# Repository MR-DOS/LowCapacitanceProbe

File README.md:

# LowCapacitanceProbe

## THIS DESIGN IS STILL UNDER CONSTRUCTION, ANY EXPORTED DATA ARE NON-FINAL AND ARE LIKELY NOT TO WORK. DO NOT ATTEMPT TO BUILD THIS DEVICE UNTIL THIS NOTICE DISAPPEARS! ALL IMAGES ARE PLACEHOLDERS AND MAY NOT FULLY REPRESENT THE REAL DEVICE AND MAY BE OUT OF SYNC WITH THE DESIGN DATA!

## USABLE DATA WILL BE PRESENT IN RELEASES TAB.

## 1+ GHz AC Probe with low input capacitance (less than 1 pF, hopefully)

2 dB flatness should be approx. 1.6 GHz, 3 dB flatness should be about 2.1 GHz, 6 dB flatness should be about 3.3 GHz. Design needs to be verified in reality (simulation is likely over-optimistic). In-band flatness should be better than 0.2 dB. Lower 6 dB corner should be at about 30 kHz while 3 dB corner is at about 50 kHz. The design should have fairly low noise, at least above 1 MHz.

Drawn in KiCAD 9.0.x, simulated in LTspice 17.x / 24.x.

## Expected issues

* Large noise at < 1 MHz due to thermal noise of 1M bias resistor
* Incorrect impedance of 50R traces
* Incorrect output impedance
* Possible instability of BF998 / spectrum peaking
* Bad linearity, especially due to use of varactor and resistor instead of current sink in source of BF998
* Large variance of parameters due to use of BF998

## Known issues which will be present

* No box yet (has to be covered in conductive material)
* Usage of obsolete part which is difficult to obtain (BF998)
* Component values not tried, will be suboptimal
* Varactor will probably need to be changed
* Needed manual calibration using a VNA and some tools
* Potentiometers not delinearised yet

## Board images (rendered)

## Live on-line project browser

[KiCanvas project viewer, disable layer Dwgs.User, view is not 1:1 with KiCAD](https://kicanvas.org/?github=https%3A%2F%2Fgithub.com%2FMR-DOS%2FLowCapacitanceProbe%2Ftree%2Fmain)

## Schematic

[Schematic SVG](https://github.com/MR-DOS/LowCapacitanceProbe/raw/main/Exports/Schematic/LowCapacitanceProbe.svg)

[Schematic PDF](https://github.com/MR-DOS/LowCapacitanceProbe/raw/main/Exports/Schematic/LowCapacitanceProbe.pdf)

## PCB drawing image

## 3D models

[STEP with solder mask, pads and copper fills (save to view)](https://github.com/MR-DOS/LowCapacitanceProbe/raw/main/Exports/3D/board.step)

[Simplified STEP (save to view)](https://github.com/MR-DOS/LowCapacitanceProbe/raw/main/Exports/3D/simplified/simplified.step)

## Board Shape

[DXF with board shape (save to view)](https://github.com/MR-DOS/LowCapacitanceProbe/raw/main/Exports/DXF/LowCapacitanceProbe-Edge_Cuts.dxf)

## Gerbers for production

[Zipped Gerbers](https://github.com/MR-DOS/LowCapacitanceProbe/raw/main/Exports/Gerbers/ZIP/LowCapacitanceProbe_v1.0.0.zip)

[Non-zipped Gerbers](https://github.com/MR-DOS/LowCapacitanceProbe/raw/main/Exports/Gerbers/)

## BOM

[Interactive BOM (save to view)](https://github.com/MR-DOS/LowCapacitanceProbe/raw/main/Exports/BOM/LowCapacitanceProbe_Interactive_BOM.html)

[CSV BOM (save to view)](https://github.com/MR-DOS/LowCapacitanceProbe/raw/main/Exports/BOM/LowCapacitanceProbe.csv)

## Jobset for exporting data

Use [this jobset (download it to view)](https://github.com/MR-DOS/LowCapacitanceProbe/raw/main/Outputs.kicad_jobset) for your designs, it is somewhat tested and should produce usable data. You can recreate all exports present in this repo using it.

## Simulation

[Simulation comparing this design and the FETProbe_V2 design (download to view)](https://github.com/MR-DOS/LowCapacitanceProbe/raw/main/Simulation/probe.asc) which works in LTspice 17.x and LTspice 24.x. Please note that you HAVE TO use alternate solver instead of normal solver (Tools -> Control Panel -> SPICE -> Engine -> Solver). The normal solver is faster, but has some stability issues and returns "hairy" traces of simulated gain which cannot be explained from electrical/physical standpoint.

## Sources for this design

Forked from [FETProbe_V2](https://github.com/makerprobe/FETProbe_V2) by makerprobe which is an improved fork of crteensy's [FETProbe_tiny](https://github.com/crteensy/FETProbe_tiny). Some ideas are taken from the FETProbe_V2, but most of the core design was changed to allow precise gain tuning, also the original design was suffering from being near stability threshold (and thus probably required the "spike filter").

The probe is also somewhat similar to my older [E-field probe](https://hackaday.io/project/169611-simple-e-field-probe) (which was just an unfinished toy for sniffing around circuits contactless) which is older than crteensy's FETProbe, but used G1 instead of G2 of BF998.

The need for stabilising resistors was found in another, even older project of mine, the [cheap TDR](https://github.com/MR-DOS/TDR_diploma_thesis). BF998 in source follower mode is prone to oscillation, especially when high impedance of capacitive characteristic is connected to its input.

## Intention of this design

First of all - I wanted to try the new KiCAD 8 and 9. It is also a development tool to make and tune a reusable jobset, design rules and checklist for checking validity of design (will be published later).

This project will try to make some RF optimalizations, usability improvements as well as (maybe) ability to use higher frequency transistor CF-739. However, there is no simulation model for CF-739, so it will have to be optimised empirically (and manually). Also, it is discontinued (like the BF998) and hard to obtain, rendering it unusable for making more than a few pieces of this probe.

Another path for improvement is to try using a JFET whch is still in production (J3xx or 2N439x).

Ability to tune the device (gain, output impedance) will be made to allow precise operation without fiddling with replacing components.

## Plans for next versions

A JFET version is planned to be tested if a JFET can replace the BF998. Even though the BF998 are not difficult to obtain, they are obsolete.
JFET simulation [can be found here (download to view)](https://github.com/MR-DOS/LowCapacitanceProbe/raw/main/Simulation/probe_jfet.asc).

Several JFETs [were found to be similar](https://github.com/MR-DOS/LowCapacitanceProbe/raw/main/Simulation/jfet_sim_notes.txt) to the BF998 in simulation. However they need to be tested.

## Other notes

If you want to figure out where your BF998 was produced, [look here](http://sp7pki.iq24.pl/default.asp?grupa=3536&temat=449565).

Beware of buying BF998R, those have reversed pinout. Also do not buy ones marked as "WMO", those are also reversed AND in smaller package than normal. ("MOW" are OK)

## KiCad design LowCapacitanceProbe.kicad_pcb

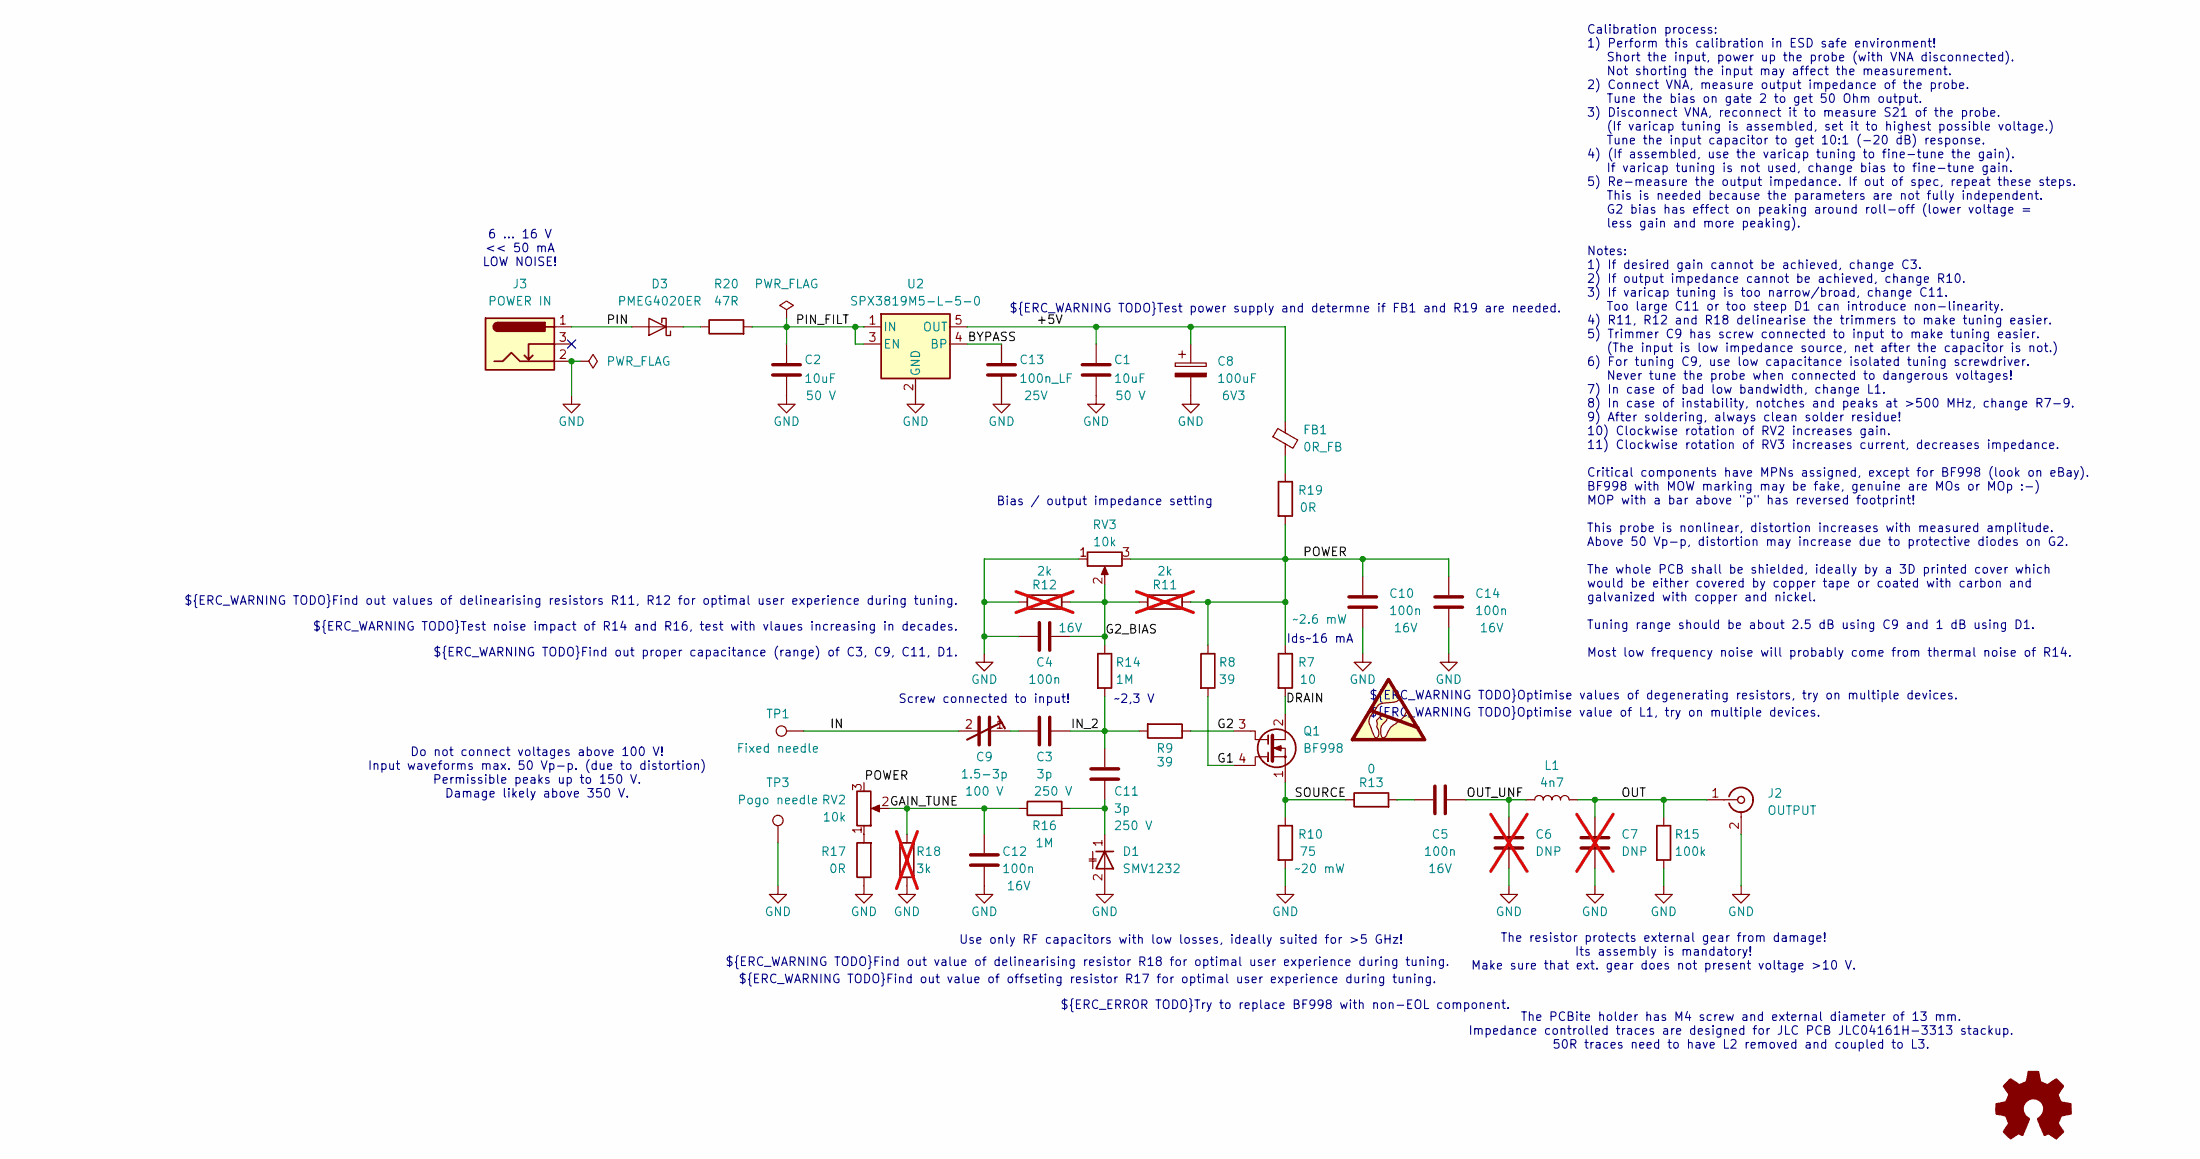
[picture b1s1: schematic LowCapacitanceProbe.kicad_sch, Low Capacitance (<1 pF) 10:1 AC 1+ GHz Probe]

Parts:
C1, C2: 10uF; C_1206_3216Metric; Rating 50 V; MPN CL31A106MBHNNNE; Mouser 187-CL31A106MBHNNNE
C3, C11: 3p; C_0402_1005Metric_Pad0.74x0.62mm_HandSolder; Rating 250 V; MPN 600F3R0CT250XT; Mouser 581-600F3R0CT
C4, C5, C10, C12, C14: 100n; C_0402_1005Metric_Pad0.74x0.62mm_HandSolder; Rating 16V; MPN 530L104KT16T; Mouser 581-530L104KT16T
C6, C7: DNP; C_0402_1005Metric_Pad0.74x0.62mm_HandSolder; not fitted
C8: 100uF; CP_EIA-3216-18_Kemet-A; Rating 6V3; MPN T55A107M6R3C0045; Mouser 74-T55A107M6R3C0045
C9: 1.5-3p; C_Trimmer_Voltronics_JR; Rating 100 V; MPN JR030; Mouser 768-JR030
C13: 100n_LF; C_0603_1608Metric_Pad1.08x0.95mm_HandSolder; Rating 25V
D1: SMV1232; D_SOD-523; MPN SMV1231-079LF; Mouser 873-SMV1231-079LF
D3: PMEG4020ER; Nexperia_CFP3_SOD-123W; MPN PMEG4020ER,115; Mouser 771-PMEG4020ER115
FB1: 0R_FB; L_0603_1608Metric_Pad1.05x0.95mm_HandSolder
J2: OUTPUT; SMA_Amphenol_132289_EdgeMount; MPN 132289; Mouser 523-132289
J3: POWER IN; BarrelJack_Wuerth_694103107102_1.35x3.9mm; MPN 694103107102; Mouser 710-694103107102
L1: 4n7; L_0402_1005Metric_Pad0.77x0.64mm_HandSolder; MPN LQG15HS4N7B02D; Mouser 81-LQG15HS4N7B02D
Q1: BF998; SOT-143
R7: 10; R_0402_1005Metric_Pad0.72x0.64mm_HandSolder; Rating ~2.6 mW
R8, R9: 39; R_0402_1005Metric_Pad0.72x0.64mm_HandSolder
R10: 75; R_0603_1608Metric_Pad0.98x0.95mm_HandSolder; Rating ~20 mW
R11, R12: 2k; R_0402_1005Metric_Pad0.72x0.64mm_HandSolder; not fitted
R13: 0; R_0402_1005Metric_Pad0.72x0.64mm_HandSolder
R14, R16: 1M; R_0603_1608Metric_Pad0.98x0.95mm_HandSolder
R15: 100k; R_0402_1005Metric_Pad0.72x0.64mm_HandSolder
R17: 0R; R_0402_1005Metric_Pad0.72x0.64mm_HandSolder
R18: 3k; R_0402_1005Metric_Pad0.72x0.64mm_HandSolder; not fitted
R19: 0R; R_0603_1608Metric_Pad0.98x0.95mm_HandSolder
R20: 47R; R_0603_1608Metric_Pad0.98x0.95mm_HandSolder
RV2, RV3: 10k; Potentiometer_Bourns_3214J_Horizontal; MPN 3214J-1-103E; Mouser 652-3214J-1-103E
SYM1: Logo_Open_Hardware_Small; OSHW-Logo2_7.3x6mm_SilkScreen
SYM3: SYM_ESD_Large; ESD-Logo_6.6x6mm_SilkScreen
TP1: Fixed needle; P50-B1_needle
TP3: Pogo needle; TestPoint_THTPad_D2.0mm_Drill1.0mm
U2: SPX3819M5-L-5-0; SOT-23-5; MPN SPX3819M5-L-5-0/TR; Mouser 701-SPX3819M5-L-50TR

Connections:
/+5V: C1.2, C8.1, FB1.1, U2.5 (OUT)
/BYPASS: C13.2, U2.4 (BP)
/DRAIN: Q1.2 (D), R7.2
/G1: Q1.4 (G2), R8.2
/G2: Q1.3 (G1), R9.1
/G2_BIAS: C4.1, R11.1, R12.2, R14.1, RV3.2
/GAIN_TUNE: C12.2, R16.1, R18.2, RV2.2
/IN: C9.2, TP1.1
/IN_2: C3.2, C11.2, R9.2, R14.2
/OUT: C7.2, J2.1 (In), L1.2, R15.1
/OUT_UNF: C5.1, C6.2, L1.1
/PIN: D3.2 (A), J3.1
/PIN_FILT: C2.2, R20.2, U2.1 (IN), U2.3 (EN)
/POWER: C10.2, C14.2, R7.1, R8.1, R11.2, R19.2, RV2.3, RV3.3
/SOURCE: Q1.1 (S), R10.1, R13.1
GND: C1.1, C2.1, C4.2, C6.1, C7.1, C8.2, C10.1, C12.1, C13.1, C14.1, D1.2 (A), J2.2 (Ext), J3.2, R10.2, R12.1, R15.2, R17.1, R18.1, RV3.1, TP3.1, U2.2 (GND)
unnamed: C3.1, C9.1
unnamed: C5.2, R13.2
unnamed: C11.1, D1.1 (K), R16.2
unnamed: D3.1 (K), R20.1
unnamed: FB1.2, R19.1
unnamed: R17.2, RV2.1

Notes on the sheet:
${ERC_WARNING TODO}Test noise impact of R14 and R16, test with vlaues increasing in decades.
Do not connect voltages above 100 V! Input waveforms max. 50 Vp-p. (due to distortion) Permissible peaks up to 150 V. Damage likely above 350 V.
${ERC_WARNING TODO}Optimise value of L1, try on multiple devices.
Use only RF capacitors with low losses, ideally suited for >5 GHz!
${ERC_WARNING TODO}Find out proper capacitance (range) of C3, C9, C11, D1.
${ERC_WARNING TODO}Find out value of offseting resistor R17 for optimal user experience during tuning.
${ERC_WARNING TODO}Find out values of delinearising resistors R11, R12 for optimal user experience during tuning.
~2,3 V
The resistor protects external gear from damage! Its assembly is mandatory! Make sure that ext. gear does not present voltage >10 V.
Bias / output impedance setting
Calibration process: 1) Perform this calibration in ESD safe environment! Short the input, power up the probe (with VNA disconnected). Not shorting the input may affect the measurement. 2) Connect VNA, measure output impedance of the probe. Tune the bias on gate 2 to get 50 Ohm output. 3) Disconnec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
${ERC_ERROR TODO}Try to replace BF998 with non-EOL component.
${ERC_WARNING TODO}Optimise values of degenerating resistors, try on multiple devices.
${ERC_WARNING TODO}Find out value of delinearising resistor R18 for optimal user experience during tuning.
Screw connected to input!
Ids~16 mA
${ERC_WARNING TODO}Test power supply and determne if FB1 and R19 are needed.
6 ... 16 V << 50 mA LOW NOISE!
The PCBite holder has M4 screw and external diameter of 13 mm. Impedance controlled traces are designed for JLC PCB JLC04161H-3313 stackup. 50R traces need to have L2 removed and coupled to L3.

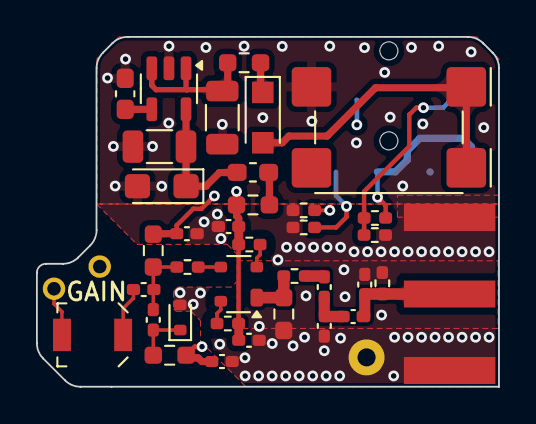
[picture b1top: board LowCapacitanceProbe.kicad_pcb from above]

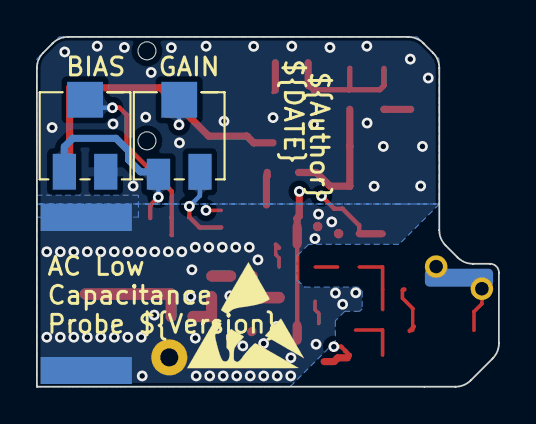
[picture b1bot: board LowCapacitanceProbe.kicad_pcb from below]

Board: 4 copper layers, 25.7 x 19.4 mm, 41 parts (4 on the bottom side), 22 nets.

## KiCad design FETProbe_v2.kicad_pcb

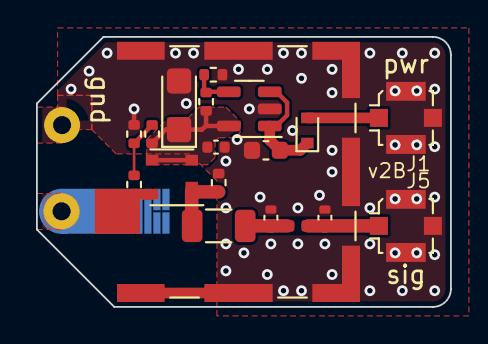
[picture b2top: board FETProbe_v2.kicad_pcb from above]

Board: 2 copper layers, 23.0 x 15.0 mm, 21 parts (0 on the bottom side), 10 nets.

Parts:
C1: 10uF; C_0402_1005Metric
C2: 10uF; C_0603_1608Metric
C4: C; input_cap
C5: 100nF; C_1206_3216Metric
C6, C7: 2.2pF; C_0402_1005Metric_mod
C8: 100uF; CP_EIA-3216-18_Kemet-A
D2: NSR0520V2T1G; D_SOD-523
J1, J5: u.Fl; U.FL_Molex_MCRF_73412-0110_Vertical
L1: 10nH; L_0402_1005Metric
N1: Laird_BMI-S-101; Laird_Technologies_BMI-S-101_13.66x12.70mm
Q1: BF998; SOT-143_mod
R1: 4k7; R_0402_1005Metric
R2: 5k6; R_0402_1005Metric
R3: 1M; R_0402_1005Metric
R4: 47R; R_0402_1005Metric
R5: 27k; R_0402_1005Metric
R6: 12k; R_0402_1005Metric
TP3: TestPoint; TestPoint_THTPad_D2.0mm_Drill1.0mm
U1: SPX3819M5-L; SOT-23-5

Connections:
4V0: C1.2, C8.1, Q1.2 (D), Q1.3 (G2), R2.2, R5.1, U1.5 (OUT)
/out: C7.2, J5.1 (In), L1.2
/out1: C5.2, C6.2, L1.1
/out2: C5.1, Q1.1 (S), R4.1
GND: C1.1, C2.1, C6.1, C7.1, C8.2, J1.2 (Ext), J5.2 (Ext), N1.1 (PAD), R1.1, R4.2, R6.2, TP3.1, U1.2 (GND)
unnamed: D2.2 (A), J1.1 (In)
unnamed: C2.2, D2.1 (K), U1.1 (IN), U1.3 (EN)
unnamed: C4.2, Q1.4 (G1), R3.2
unnamed: R1.2, R2.1, R3.1
unnamed: R5.2, R6.1, U1.4 (ADJ)

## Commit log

2024-09-24 Create LICENSE
2024-09-24 update usage pdf
2025-02-24 Tiny change to readme
2025-02-24 Added simulation which should solve instabilities at high frequencies as well as unmatched output impedance (was about 30 Ohm).
2025-02-25 added gitignore, slight touches to simulation, removed files from previous design version made by MakerProbe
2025-02-25 Finished simulation, in simulation the probe was extended from 1.3 GHz to 1.68 GHz [2 dB] (or from 1.87 to 3.3 GHz [6 dB]). Flatness was greatly improved, roll-off now nearly approximates first order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
2025-02-25 Fixed gitignore
2025-02-25 Removed old simulation outputs
2025-02-25 Updated README to match simulation results.
2025-02-25 Slight fixes to simulation, started modifying schematics.
2025-02-26 Added more possibilities for tuning gain, added delinearization networks for easier fine-tuning, increased power supply voltage, fixed BF998 symbol. Added simulation of delinearization networks.
2025-02-28 Added calibration notes, fixed delinearization for gate bias
2025-02-28 Added footprints to all components, added MPNs and Mouser numbers to critical components. Added some notes.
2025-02-28 refresh after save
2025-02-28 Changed output connector to SMA, changed diode for more common one.
2025-03-01 Reduced peak current during connection of power, replaced LDO from adjustable version by 5V, lowered noise of LDO.
2025-03-01 Added net labels, synchronised PCB with SCH, grouped all elements.
2025-03-01 Slight fixes, simulation modified for varicap analysis and noise analysis, started routing of PCB.
2025-03-02 Replaced trimmers by smaller SMT types, continued routing.
2025-03-03 Added mounting point for PCBite holder (M4 nut).
2025-03-03 Continued routing, modifications for better usability.
2025-03-07 Synchronisation of computers, some tiny changes to simulation.
2025-03-10 Continued routing, replaced power connector.
2025-03-11 Replaced trimmers, added 3D models, continued routing and placing.
2025-03-12 Further work on routing, change to 4 layers is imminent.
2025-03-13 Added first try at output jobset.
2025-03-13 Added links to images
2025-03-13 Fix image links
2025-03-13 Add notice about the project being unfinished.
2025-03-13 mORE DISCLAIMERS
2025-03-15 More routing
2025-03-18 Some more routing, modified outjob.
2025-03-20 Additional routing, finalizing PCB shape.
2025-03-21 Started adding JLCPCB rules, board rules, net classes, component classes, custom DRC rules, finishing board, RF traces for JLCPCB 4L 3313, unmasked outline for conductive case etc.
2025-03-21 Refreshed exports
2025-03-23 Added footprint and model of P50 broken needle and whole pogo with sleeve. Finalizing shape and ground contacts.
2025-03-26 Some macdinking, review/checklist in progress.
2025-03-31 Final finishing touches, checking.
2025-03-31 Removing temporary files.
2025-04-08 Finishing PCB, toying with jobset, exporting data.
2025-04-08 Fixed images
2025-04-10 Finishing data, completing jobset, ready to send to JLC PCB.
2025-04-11 Fixed some RF traces, copper fills, added some teardrops.
2025-04-11 Some more fixes to GND fill, added board stackup and board characteristics.
2025-04-14 Fiddling with jobset, updating readme.
2025-04-14 Fixed BOM in gitignore, added KiCanvas link.
2025-04-14 Added link details due to Github providing files as text.
2025-04-14 Added PCB drawing export to jobset + data.
2025-04-14 Fixed link in readme
2025-04-14 Added jobset info.
2025-04-23 Fixed jobset to use relative paths everywhere
2025-04-23 A bit of cleanup, updated readme
2025-04-23 Readme header fix
2025-04-25 Optimised simulation for performance to 3+ GHz. More notes about JFET replacements.
2025-04-25 Forgot to save simulation.
